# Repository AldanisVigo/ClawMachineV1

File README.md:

#Vigo's Claw Machine V1.0
#Previews

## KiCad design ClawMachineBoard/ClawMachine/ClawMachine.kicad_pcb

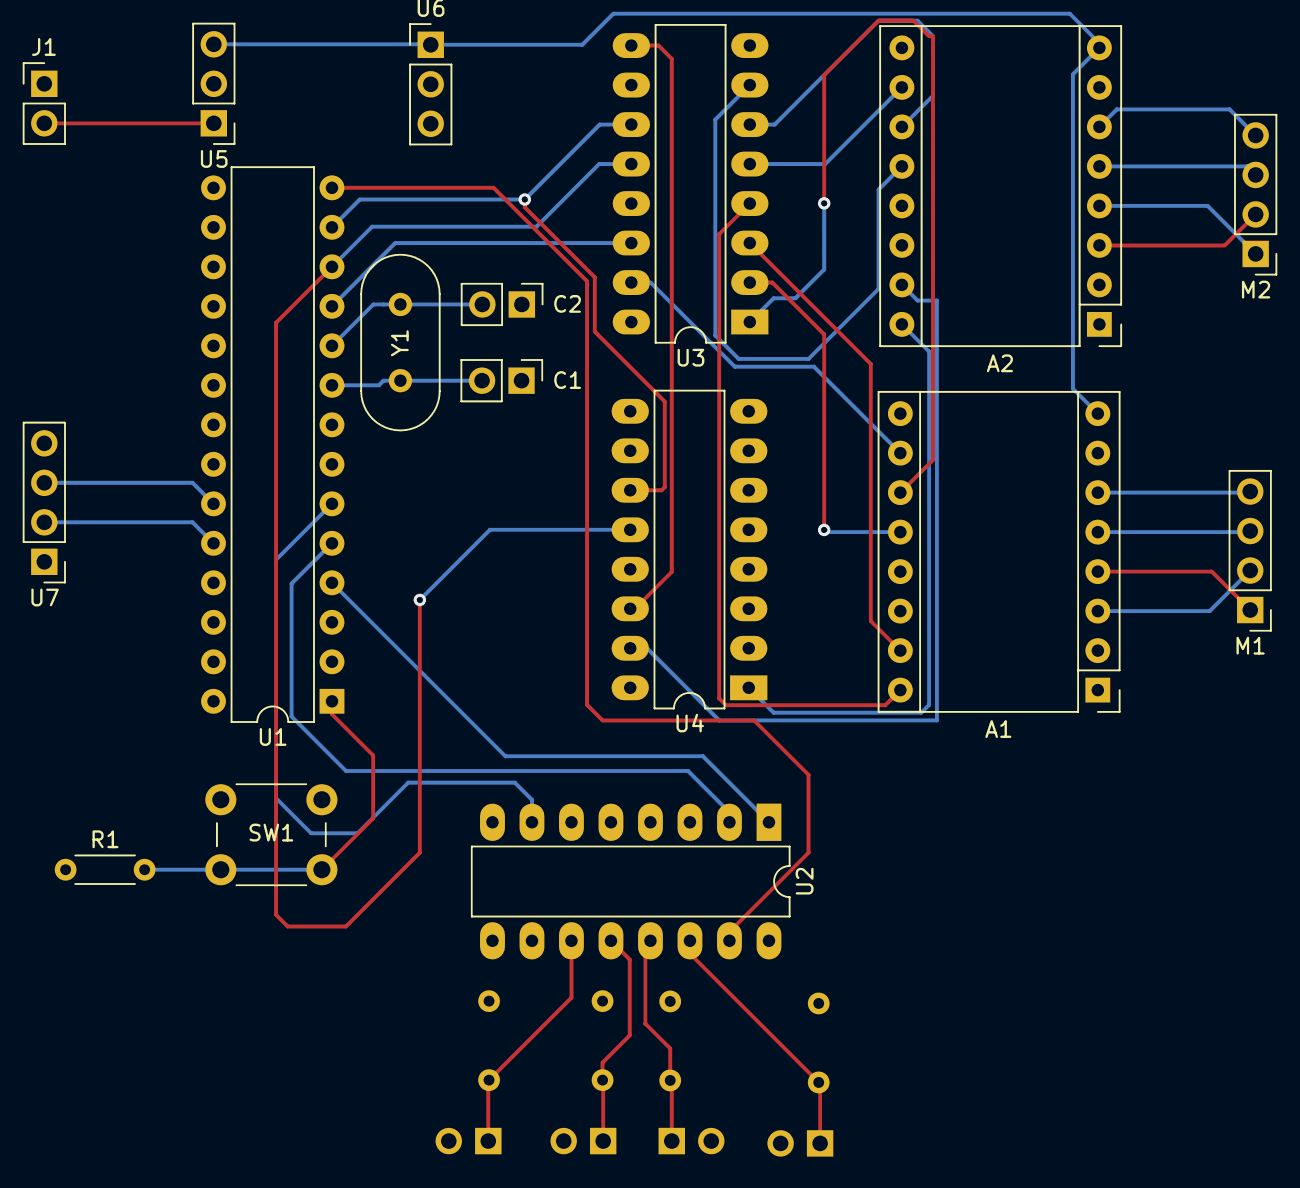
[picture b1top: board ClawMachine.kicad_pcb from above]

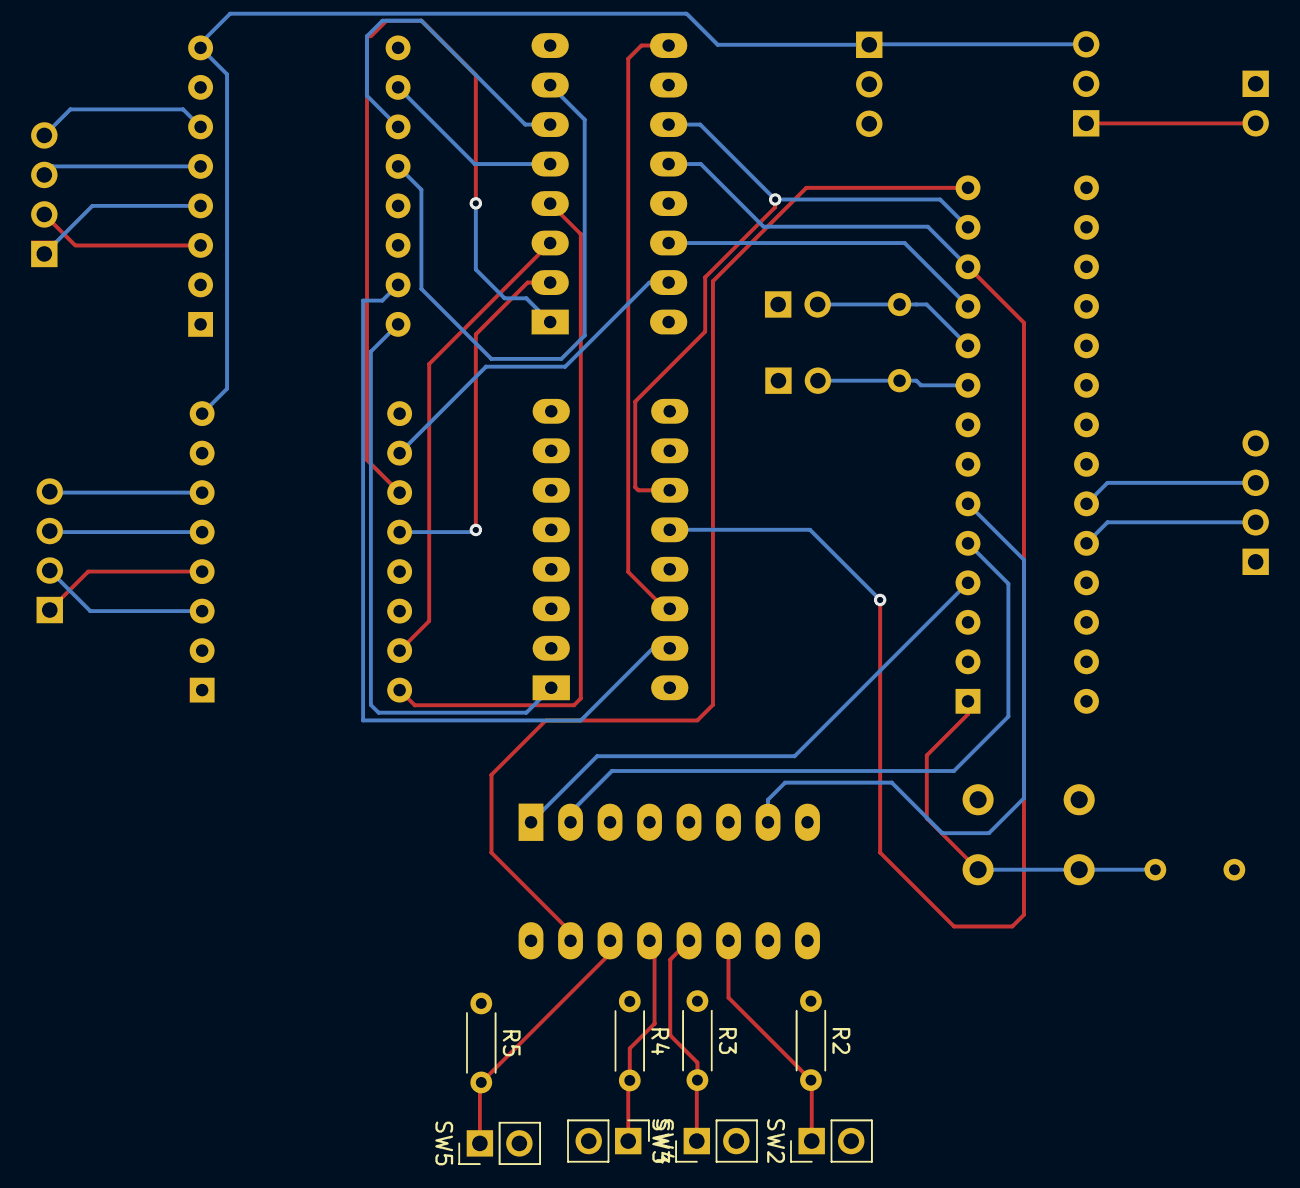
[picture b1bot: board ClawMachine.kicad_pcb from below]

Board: 4 copper layers, 25 parts (8 on the bottom side), 39 nets.

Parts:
A1, A2: Pololu_Breakout_A4988; Pololu_Breakout-16_15.2x20.3mm
C1, C2: 22pF; PinHeader_1x02_P2.54mm_Vertical
J1: Power In; PinHeader_1x02_P2.54mm_Vertical
M1: X Axis Stepper; PinHeader_1x04_P2.54mm_Vertical
M2: Y Axis Stepper; PinHeader_1x04_P2.54mm_Vertical
R1: 10KΩ; R_Axial_DIN0204_L3.6mm_D1.6mm_P5.08mm_Horizontal
R2, R3, R4, R5: 250Ω; R_Axial_DIN0204_L3.6mm_D1.6mm_P5.08mm_Horizontal
SW1: RESET SW; SW_PUSH_6mm
SW2, SW3, SW4, SW5: SW_DIP_x01; PinHeader_1x02_P2.54mm_Vertical
U1: ATmega328-PU; DIP-28_W7.62mm
U2: 74LS165; DIP-16_W7.62mm_LongPads
U3, U4: 74LS595; DIP-16_W7.62mm_LongPads
U5: L7812; PinHeader_1x03_P2.54mm_Vertical
U6: L7805; PinHeader_1x03_P2.54mm_Vertical
U7: ParallaxJoystick; PinHeader_1x04_P2.54mm_Vertical
Y1: 16Mhz; Crystal_HC18-U_Vertical

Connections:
+5V: A1.2, A1.13, A1.14, A2.2, A2.13, A2.14, R1.1, R2.1, R3.1, R4.1, R5.1, U1.7, U2.16, U3.10, U3.16, U4.10, U4.16, U6.3, U7.1
+12V: J1.2, U5.1
GND: A1.1, A1.7, A1.9, A2.1, A2.7, A2.9, C1.1, C2.1, J1.1, SW1.2, SW2.2, SW3.2, SW4.2, SW5.2, U1.8, U1.22, U2.8, U3.8, U3.13, U4.8, U4.13, U5.2, U6.2, U7.4
unnamed: A1.3, M1.2
unnamed: A1.4, M1.1
unnamed: A1.5, M1.3
unnamed: A1.6, M1.4
unnamed: A1.8, A2.8, U5.3, U6.1
unnamed: A1.10, U3.15
unnamed: A1.11, U3.1
unnamed: A1.12, U3.2
unnamed: A1.15, U3.3
unnamed: A1.16, U3.4
unnamed: A2.3, M2.2
unnamed: A2.4, M2.1
unnamed: A2.5, M2.3
unnamed: A2.6, M2.4
unnamed: A2.10, U3.5
unnamed: A2.11, U3.6
unnamed: A2.12, U3.7
unnamed: A2.15, U4.15
unnamed: A2.16, U4.1
unnamed: C1.2, U1.9, Y1.2
unnamed: C2.2, U1.10, Y1.1
unnamed: R1.2, SW1.1, U1.1
unnamed: R2.2, SW2.1, U2.11
unnamed: R3.2, SW3.1, U2.12
unnamed: R4.2, SW4.1, U2.13
unnamed: R5.2, SW5.1, U2.14
unnamed: U1.4, U2.1
unnamed: U1.5, U2.2
unnamed: U1.6, U2.7
unnamed: U1.11, U3.14
unnamed: U1.12, U3.12, U4.12
unnamed: U1.13, U3.11, U4.11
unnamed: U1.14, U2.15
unnamed: U1.23, U7.3
unnamed: U1.24, U7.2
unnamed: U3.9, U4.14

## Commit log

2023-08-04 first push
2023-08-04 added readme
2023-08-04 fixed images in readme
